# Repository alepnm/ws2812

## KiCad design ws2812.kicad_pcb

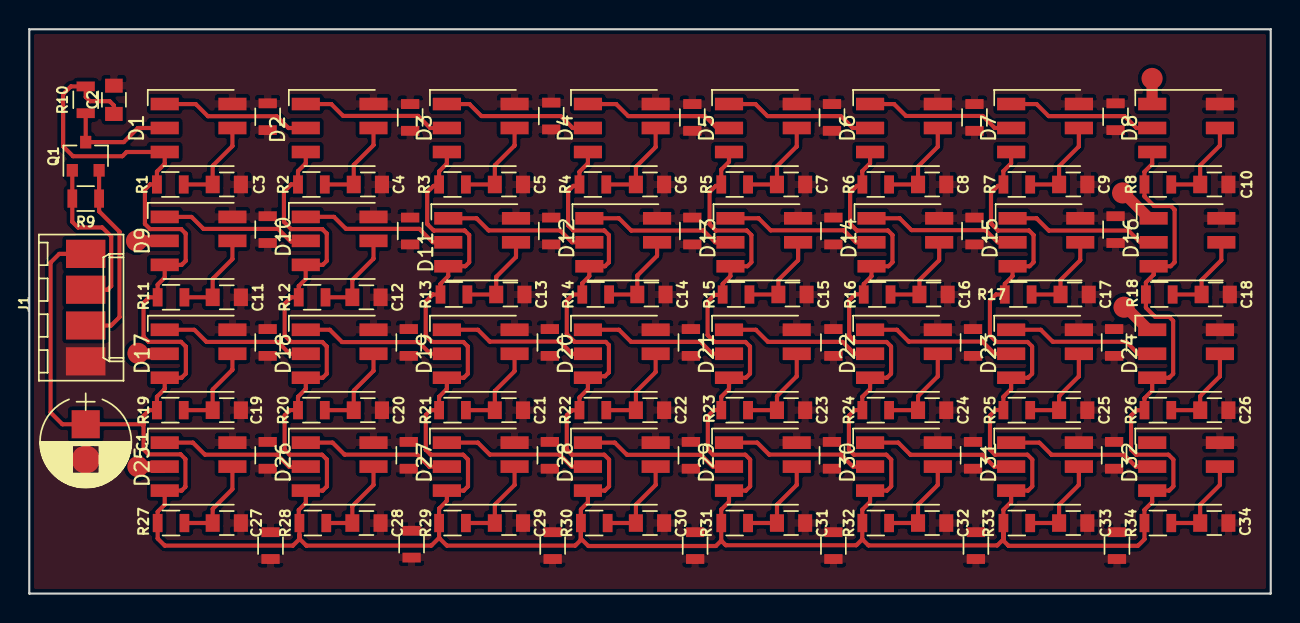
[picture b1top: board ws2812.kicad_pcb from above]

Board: 2 copper layers, 88.0 x 40.0 mm, 137 parts (0 on the bottom side), 68 nets.

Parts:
C1: 100uFx16V; CP_Radial_D6.3mm_P2.50mm
C2, C3, C4, C5, C6, C7, C8, C9, C10, C11, C12, C13, C14, C15, C16, C17, C18, C19, C20, C21, C22, C23, C24, C25, C26, C27, C28, C29, C30, C31, C32, C33, C34: 100n; C_0805
D1, D2, D3, D4, D5, D6, D7, D8, D9, D10, D11, D12, D13, D14, D15, D16, D17, D18, D19, D20, D21, D22, D23, D24, D25, D26, D27, D28, D29, D30, D31, D32: WS2812; LED_RGB_5050-6
J1: X_WF-04S; Molex_KK-6410-04_04x2.54mm_Straight
JP1, JP2, JP3, JP4, JP5, JP6, JP7, JP8, JP9, JP10, JP11, JP12, JP13, JP14, JP15, JP16, JP17, JP18, JP18#2, JP19, JP19#2, JP20, JP20#2, JP21, JP21#2, JP22, JP23, JP24, JP25, JP26, JP27, JP28, JP29, JP30, JP31: 0R; R_0805
Q1: IRLML2502; SOT-23
R1, R2, R3, R4, R5, R6, R7, R8, R11, R12, R13, R14, R15, R16, R17, R18, R19, R20, R21, R22, R23, R24, R25, R26, R27, R28, R29, R30, R31, R32, R33, R34: 120R; R_0805
R9, R10: 10k; R_0805

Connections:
/3VDC: J1.3, Q1.1, R9.2
/DATA1: D8.1, D9.2
/DATA2: D16.1, D17.2
/DATA3: D24.1, D25.2
/DATAIN: J1.2, Q1.2, R9.1
/DIN: D1.2, Q1.3, R10.1
GND: C1.2, C2.2, C3.2, C4.2, C5.2, C6.2, C7.2, C8.2, C9.2, C10.2, C11.2, C12.2, C13.2, C14.2, C15.2, C16.2, C17.2, C18.2, C19.2, C20.2, C21.2, C22.2, C23.2, C24.2, C25.2, C26.2, C27.2, C28.2, C29.2, C30.2, C31.2, C32.2, C33.2, C34.2, D1.6, D2.6, D3.6, D4.6, D5.6, D6.6, D7.6, D8.6, D9.6, D10.6, D11.6, D12.6, D13.6, D14.6, D15.6, D16.6, D17.6, D18.6, D19.6, D20.6, D21.6, D22.6, D23.6, D24.6, D25.6, D26.6, D27.6, D28.6, D29.6, D30.6, D31.6, D32.6, J1.1, JP1.1, JP1.2, JP2.1, JP2.2, JP3.1, JP3.2, JP4.1, JP4.2, JP5.1, JP5.2, JP6.1, JP6.2, JP7.1, JP7.2, JP8.1, JP8.2, JP9.1, JP9.2, JP10.1, JP10.2, JP11.1, JP11.2, JP12.1, JP12.2, JP13.1, JP13.2, JP14.1, JP14.2, JP15.1, JP15.2, JP16.1, JP16.2, JP17.1, JP17.2, JP18.1, JP18.2, JP18#2.1, JP18#2.2, JP19.1, JP19.2, JP19#2.1, JP19#2.2, JP20.1, JP20.2, JP20#2.1, JP20#2.2, JP21.1, JP21.2, JP21#2.1, JP21#2.2, JP22.1, JP22.2, JP23.1, JP23.2, JP24.1, JP24.2, JP25.1, JP25.2, JP26.1, JP26.2, JP27.1, JP27.2, JP28.1, JP28.2, JP29.1, JP29.2, JP30.1, JP30.2, JP31.1, JP31.2
unnamed: C3.1, D1.5, R1.1
unnamed: C4.1, D2.5, R2.1
unnamed: C5.1, D3.5, R3.1
unnamed: C6.1, D4.5, R4.1
unnamed: C7.1, D5.5, R5.1
unnamed: C8.1, D6.5, R6.1
unnamed: C9.1, D7.5, R7.1
unnamed: C10.1, D8.5, R8.1
unnamed: C11.1, D9.5, R11.1
unnamed: C12.1, D10.5, R12.1
unnamed: C13.1, D11.5, R13.1
unnamed: C14.1, D12.5, R14.1
unnamed: C15.1, D13.5, R15.1
unnamed: C16.1, D14.5, R16.1
unnamed: C17.1, D15.5, R17.1
unnamed: C18.1, D16.5, R18.1
unnamed: C19.1, D17.5, R19.1
unnamed: C20.1, D18.5, R20.1
unnamed: C21.1, D19.5, R21.1
unnamed: C22.1, D20.5, R22.1
unnamed: C23.1, D21.5, R23.1
unnamed: C24.1, D22.5, R24.1
unnamed: C25.1, D23.5, R25.1
unnamed: C26.1, D24.5, R26.1
unnamed: C27.1, D25.5, R27.1
unnamed: C28.1, D26.5, R28.1
unnamed: C29.1, D27.5, R29.1
unnamed: C30.1, D28.5, R30.1
unnamed: C31.1, D29.5, R31.1
unnamed: C32.1, D30.5, R32.1
unnamed: C33.1, D31.5, R33.1
unnamed: C34.1, D32.5, R34.1
unnamed: D1.1, D2.2
unnamed: D2.1, D3.2
unnamed: D3.1, D4.2
unnamed: D4.1, D5.2
unnamed: D5.1, D6.2
unnamed: D6.1, D7.2
unnamed: D7.1, D8.2
unnamed: D10.1, D11.2
unnamed: D9.1, D10.2
unnamed: D11.1, D12.2
unnamed: D12.1, D13.2
unnamed: D13.1, D14.2
unnamed: D14.1, D15.2
unnamed: D15.1, D16.2
unnamed: D17.1, D18.2
unnamed: D18.1, D19.2
unnamed: D19.1, D20.2
unnamed: D20.1, D21.2
unnamed: D21.1, D22.2
unnamed: D22.1, D23.2
unnamed: D23.1, D24.2
unnamed: D25.1, D26.2
unnamed: D26.1, D27.2
unnamed: D27.1, D28.2
unnamed: D28.1, D29.2
unnamed: D29.1, D30.2
unnamed: D30.1, D31.2
unnamed: D31.1, D32.2
VCC: C1.1, C2.1, D1.3, D2.3, D3.3, D4.3, D5.3, D6.3, D7.3, D8.3, D9.3, D10.3, D11.3, D12.3, D13.3, D14.3, D15.3, D16.3, D17.3, D18.3, D19.3, D20.3, D21.3, D22.3, D23.3, D24.3, D25.3, D26.3, D27.3, D28.3, D29.3, D30.3, D31.3, D32.3, J1.4, R1.2, R2.2, R3.2, R4.2, R5.2, R6.2, R7.2, R8.2, R10.2, R11.2, R12.2, R13.2, R14.2, R15.2, R16.2, R17.2, R18.2, R19.2, R20.2, R21.2, R22.2, R23.2, R24.2, R25.2, R26.2, R27.2, R28.2, R29.2, R30.2, R31.2, R32.2, R33.2, R34.2

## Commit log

2018-07-25 pradine inicializacija
2018-07-25 sablono failu paruosimas
